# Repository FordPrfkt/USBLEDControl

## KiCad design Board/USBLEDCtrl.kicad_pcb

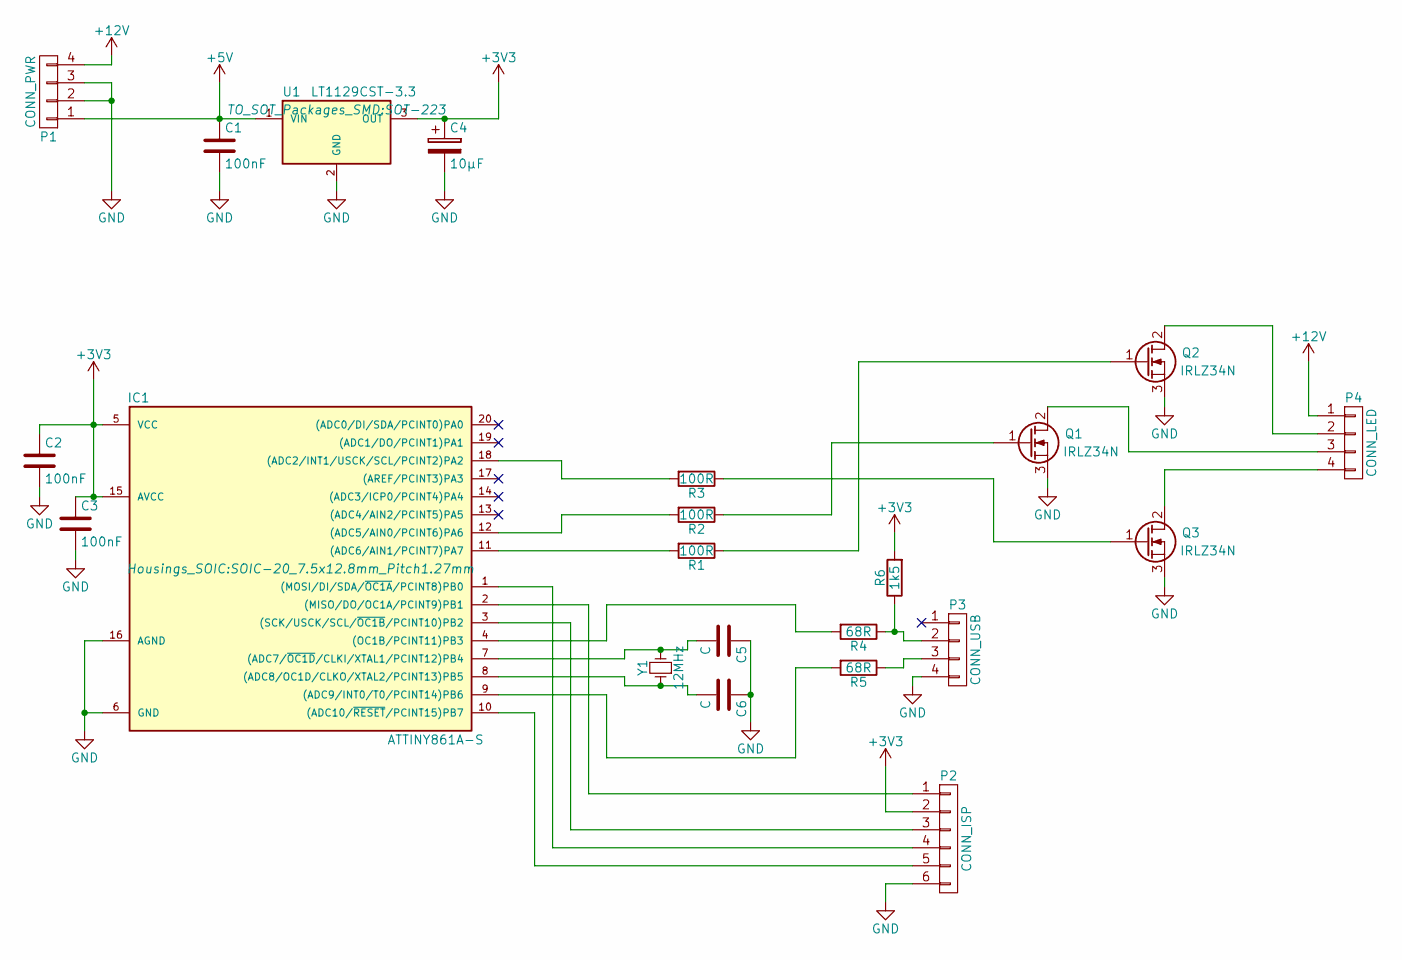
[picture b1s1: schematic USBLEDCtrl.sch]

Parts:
C1, C2, C3: 100nF; C_0603
C4: 10µF; TantalC_SizeB_EIA-3528_HandSoldering
C5, C6: C; C_0603
IC1: ATTINY861A-S; SOIC-20_7.5x12.8mm_Pitch1.27mm
P1: CONN_PWR; conn_hdd_15-24-4449
P2: CONN_ISP; Pin_Header_Straight_2x03
P3: CONN_USB; Pin_Header_Angled_1x04
P4: CONN_LED; bornier4
Q1, Q2, Q3: IRLZ34N; TO-220_Neutral123_Horizontal
R1, R2, R3: 100R; R_0603
R4, R5: 68R; R_0603
R6: 1k5; R_0603
U1: LT1129CST-3.3; SOT-223
Y1: 12MHz; Crystal_HC49-U_Vertical

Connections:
+3V3: C2.1, C3.1, C4.1, IC1.5 (VCC), IC1.15 (AVCC), P2.2, R6.2, U1.3 (OUT)
+5V: C1.1, P1.1, U1.1 (VIN)
+12V: P1.4, P4.1
GND: C1.2, C2.2, C3.2, C4.2, C5.1, C6.1, IC1.6 (GND), IC1.16 (AGND), P1.2, P1.3, P2.6, P3.4, Q1.3 (S), Q2.3 (S), Q3.3 (S), U1.2 (GND)
unnamed: C5.2, IC1.7 ((ADC7/~OC1D~/CLKI/XTAL1/PCINT12)PB4), Y1.2
unnamed: C6.2, IC1.8 ((ADC8/OC1D/CLKO/XTAL2/PCINT13)PB5), Y1.1
unnamed: IC1.1 ((MOSI/DI/SDA/~OC1A~/PCINT8)PB0), P2.4
unnamed: IC1.2 ((MISO/DO/OC1A/PCINT9)PB1), P2.1
unnamed: IC1.3 ((SCK/USCK/SCL/~OC1B~/PCINT10)PB2), P2.3
unnamed: IC1.4 ((OC1B/PCINT11)PB3), R4.2
unnamed: IC1.9 ((ADC9/INT0/T0/PCINT14)PB6), R5.2
unnamed: IC1.10 ((ADC10/~RESET~/PCINT15)PB7), P2.5
unnamed: IC1.11 ((ADC6/AIN1/PCINT7)PA7), R1.2
unnamed: IC1.12 ((ADC5/AIN0/PCINT6)PA6), R2.2
unnamed: IC1.18 ((ADC2/INT1/USCK/SCL/PCINT2)PA2), R3.2
unnamed: P3.2, R4.1, R6.1
unnamed: P3.3, R5.1
unnamed: P4.2, Q2.2 (D)
unnamed: P4.3, Q1.2 (D)
unnamed: P4.4, Q3.2 (D)
unnamed: Q1.1 (G), R2.1
unnamed: Q2.1 (G), R1.1
unnamed: Q3.1 (G), R3.1

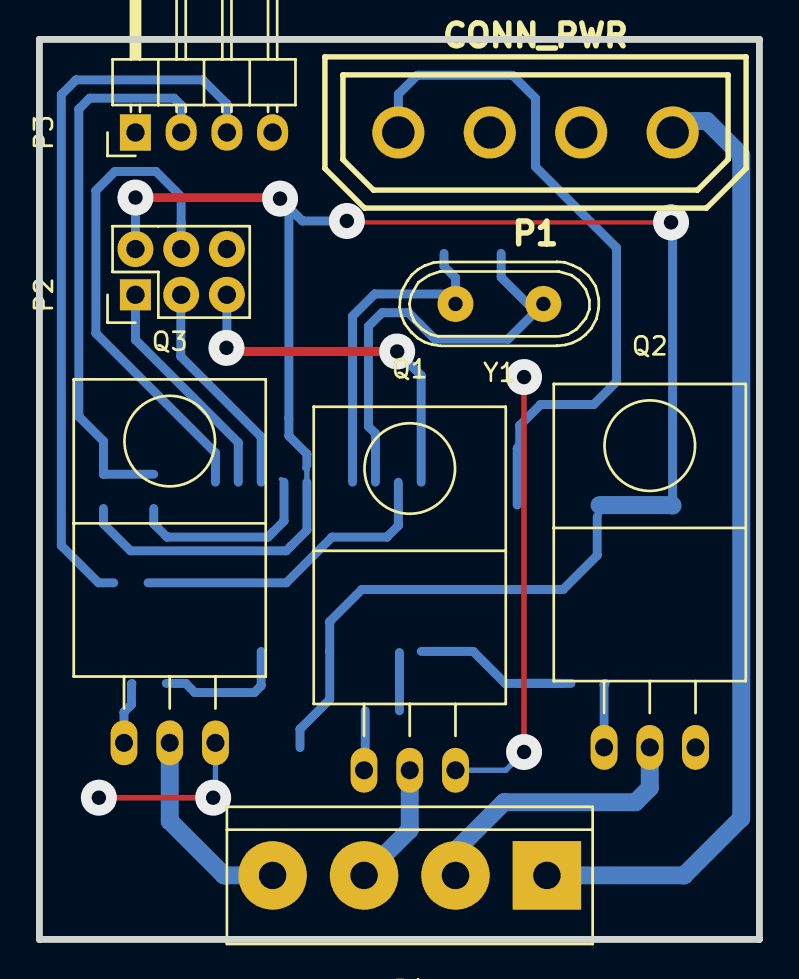
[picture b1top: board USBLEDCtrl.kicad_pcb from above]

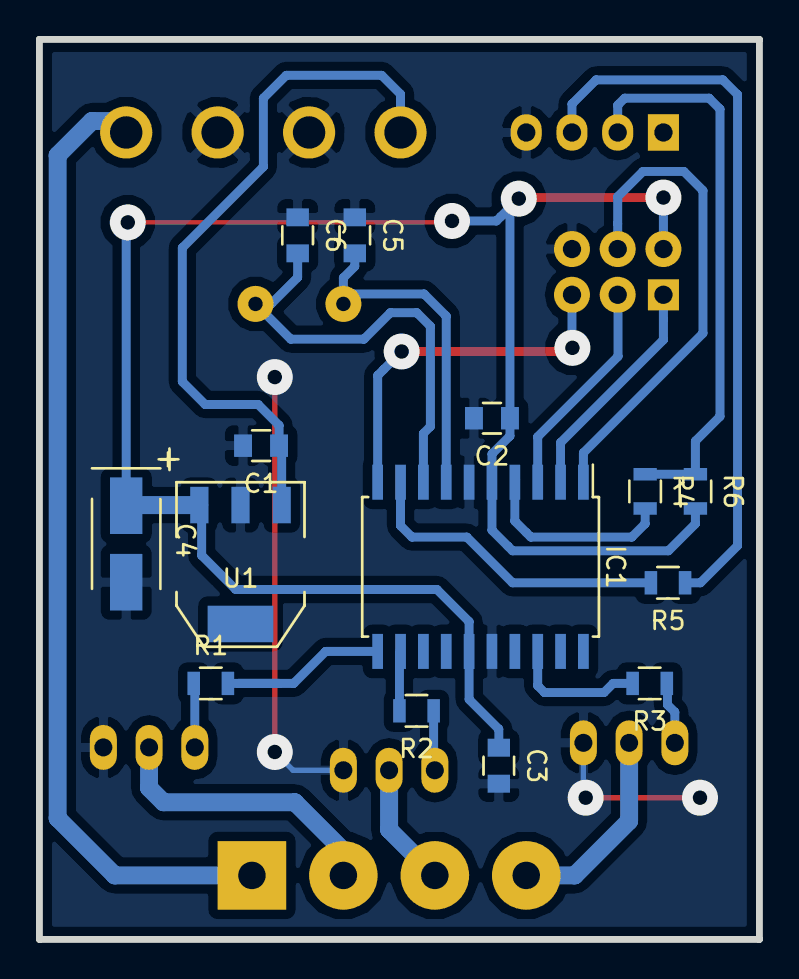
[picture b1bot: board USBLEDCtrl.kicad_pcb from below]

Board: 2 copper layers, 40.0 x 50.0 mm, 22 parts (14 on the bottom side), 23 nets.

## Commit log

2016-03-01 Datei entfernt
2016-03-05 Kleine Layoutänderung
2016-03-05 Create gh-pages branch via GitHub
2016-03-27 Grössere Restringe
2016-08-28 Layout done
2016-08-28 Plot hinzugefügt
